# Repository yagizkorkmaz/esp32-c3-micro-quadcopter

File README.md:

# ESP32-C3 Micro Quadcopter

A brushed-motor micro quadcopter built around a custom flight-controller PCB: ESP32-C3 SuperMini, MPU-6050 IMU, a buck-boost regulator that keeps the MCU alive when the battery sags, and four low-side MOSFET motor drivers.

**Status: in progress.** Rev A boards are fabricated. Next: assembly, bring-up and flight firmware.

*Rev A, as it came back from the fab.*

## Hardware overview

```
1S LiPo ──┬── TPS63001 buck-boost ── 3.3 V ──┬── ESP32-C3 SuperMini (flight control, planned ESP-NOW link)
          │                                  └── MPU-6050 IMU (I2C)
          ├── 47k / 47k divider ── ADC (battery voltage)
          └── motor + ──[8520 motor]── AO3400A ── GND      (x4, PWM from ESP32-C3)
```

| Item | Choice | Why |
|---|---|---|
| MCU | ESP32-C3 SuperMini module | Small, cheap, built-in radio for a planned ESP-NOW controller link |
| IMU | MPU-6050 (GY-521 module), I2C | 3-axis gyro + accelerometer for attitude estimation |
| Regulator | TI TPS63001 buck-boost, 1S LiPo → 3.3 V | Holds 3.3 V when motor current pulls the battery below 3.3 V, so the MCU does not brown out mid-flight |
| Inductor | 2.2 µH, Bourns SRN4018-2R2M | Value from the TPS63001 reference design |
| Motor drivers | 4× AO3400A N-MOSFET, low side | Logic-level gate, driven directly by ESP32-C3 PWM |
| Gate network | 100 Ω series + 10 kΩ pull-down per MOSFET | Limits gate current; keeps the motors off while the MCU boots |
| Flyback diodes | 4× SS34 Schottky | Clamp the motor's inductive kick when the MOSFET turns off |
| Battery sense | 47 kΩ / 47 kΩ divider + 100 nF | Halves the cell voltage into the ADC range |
| Bulk capacitor | 220 µF / 6.3 V low-ESR | Buffers motor current transients on the battery rail |
| Motors | 4× 8520 coreless brushed, 3.7 V | |
| Battery | 1S LiPo | |

The TPS63001 section follows the TI reference design: the fixed 3.3 V version with FB tied to VOUT, a 100 Ω / 100 nF filter on VINA, EN and PS/SYNC tied to VINA, 10 µF at the input and 2× 10 µF at the output.

### ESP32-C3 pin map

| GPIO | Function |
|---|---|
| GPIO3 | Motor 1 PWM (Q1 gate via R1) |
| GPIO4 | Motor 2 PWM (Q2 gate via R3) |
| GPIO6 | Motor 3 PWM (Q3 gate via R5) |
| GPIO7 | Motor 4 PWM (Q4 gate via R7) |
| GPIO5 | MPU-6050 SDA |
| GPIO10 | MPU-6050 SCL |
| GPIO0 | Battery voltage (ADC, 47k / 47k divider) |

The MPU-6050 AD0 pin is tied to GND, so the IMU sits at I2C address 0x68. Its INT pin is not connected.

## PCB

| Item | Value |
|---|---|
| Size | 53 × 84 mm |
| Layers | 2 |
| Thickness | 0.8 mm as ordered (the board file still lists 1.6 mm) |
| Placement | All 34 components on the top side; all routing on the top layer |
| Ground | Ground pour on the bottom layer; SMD ground pads tied to it with 16 vias |
| Tool | KiCad |

KiCad 10 schematic and board files are in `hardware/`.

## Rev A notes

Found during design review after the boards were ordered. Each item has a fix that does not need a new board.

1. **ESP32-C3 GND pin is not connected.** The schematic symbol numbers its power pins `-1`, `-2`, `-3`, while the footprint pads are named `5V`, `G`, `3.3`. The pad names did not match, so the `G` pad got no net.
   *Rev A fix:* bridge the `G` pad to the ground pour on the bottom side with solder, or run a short wire to GND.
   *Rev B:* match the symbol pin numbers to the footprint and run ERC before ordering.
2. **Motor power runs on 0.2 mm tracks.** Every track on the board is 0.2 mm, including the battery-to-motor path. That is fine for signals, but four 8520 motors draw several amps, and the tracks to the far motors are 75–95 mm long.
   *Rev A fix:* wire from the battery `+` pad to each motor `+` pad.
   *Rev B:* route with the track tool and net classes instead of graphic lines on copper, with at least 1.5–2 mm for the battery rail and 1 mm for the motor and drain tracks.
3. **Battery and motors on 2.54 mm headers.** Header pins are rated for a few amps; the motors together can pull 8–10 A at full throttle.
   *Rev A fix:* solder the battery and motor leads directly to the pads.
   *Rev B:* use a high-current battery connector (BT2.0 / XT30).

## Bring-up plan

1. Before power: check continuity from `G` to battery `−`, and check for no short between battery `+` and `−`.
2. First power from a current-limited supply (3.7 V, 0.5 A limit) instead of the battery.
3. Confirm 3.3 V on the ESP32-C3 `3.3` pin, then flash.
4. Read the MPU-6050 over I2C.
5. Spin each motor on its own, propellers off.
6. Flight firmware: attitude estimation from the MPU-6050 and a PID loop driving the four motors, with an ESP-NOW link to a controller.

## Repository layout

```
hardware/   KiCad 10 schematic (drone.kicad_sch) and PCB (drone.kicad_pcb)
docs/       photos
```

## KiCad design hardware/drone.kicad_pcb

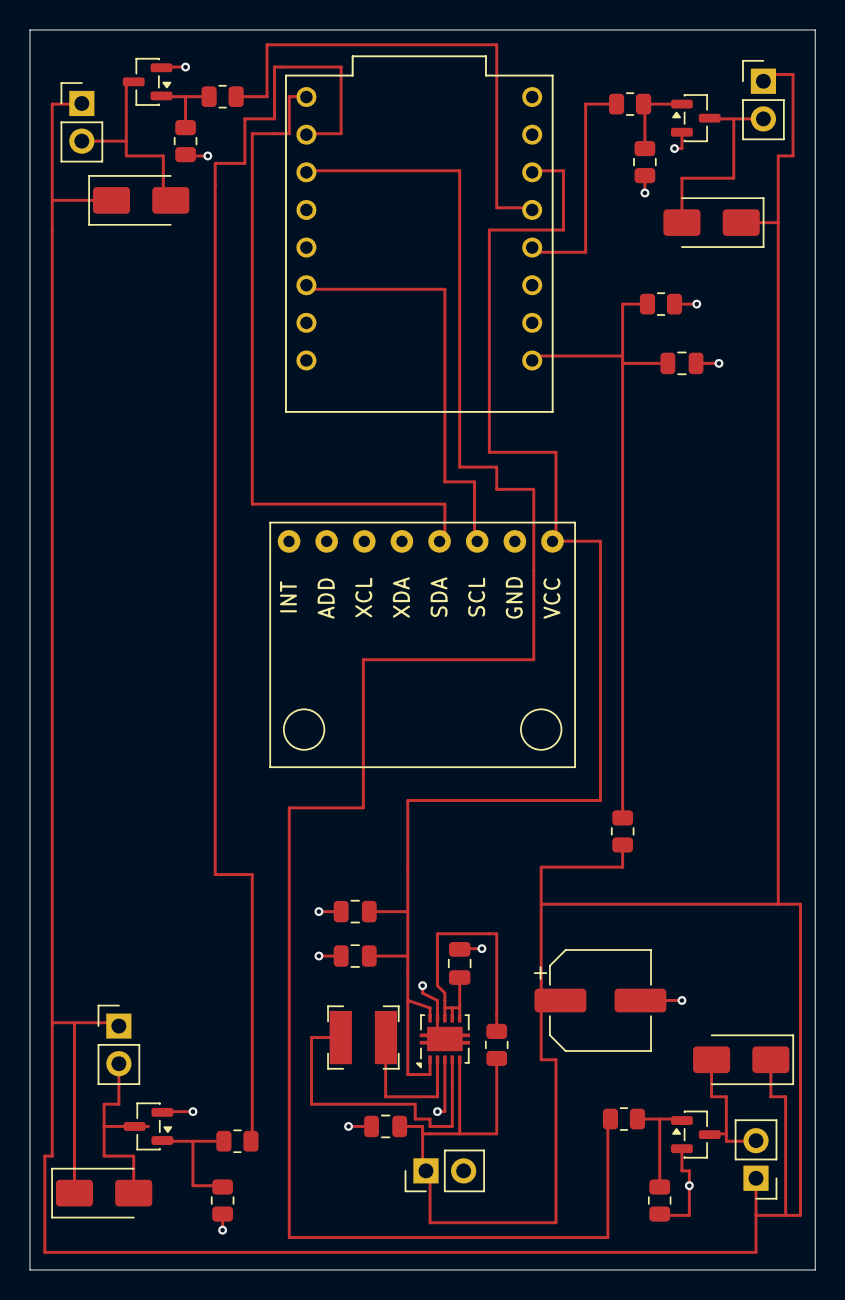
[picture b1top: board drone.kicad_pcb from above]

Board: 2 copper layers, 53.0 x 83.7 mm, 34 parts (0 on the bottom side), 21 nets, no tracks yet.

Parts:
C1, C2, C3: 10u; C_0805_2012Metric
C4, C6: 100n; C_0805_2012Metric
C5: 220u; CP_Elec_6.3x5.8
D1, D2, D3, D4: SS34; D_SMA
L1: 2.2u; L_Bourns-SRN4018
Q1, Q2, Q3, Q4: AO3400A; SOT-23
R1, R3, R5, R7, R9: 100; R_0805_2012Metric
R2, R4, R6, R8: 10k; R_0805_2012Metric
R10, R11: 47k; R_0805_2012Metric
U1: ESP32_C3_Super_Mini; MODULE_ESP32-C3_SUPERMINI_TH
U2: TPS63001; Texas_DRC0010J
U3: module_mpu6050
batarya1: Conn_01x02; PinHeader_1x02_P2.54mm_Vertical
motor1, motor2, motor3, motor4: Conn_01x02; PinHeader_1x02_P2.54mm_Vertical

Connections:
GND: C1.1, C2.2, C3.2, C4.1, C5.2, C6.2, Q1.2 (S), Q2.2 (S), Q3.2 (S), Q4.2 (S), R2.2, R4.2, R6.2, R8.2, R11.2, U2.3 (PGND), U2.9 (GND), U2.11 (PGND), U3.2 (GND), U3.7 (ADD), batarya1.2
unnamed: D1.2 (A), Q1.3 (D), motor1.2
unnamed: C1.2, C5.1, D1.1 (K), D2.1 (K), D3.1 (K), D4.1 (K), R9.1, R10.1, U2.5 (VIN), batarya1.1, motor1.1, motor2.1, motor3.1, motor4.1
unnamed: D2.2 (A), Q2.3 (D), motor2.2
unnamed: D3.2 (A), Q3.3 (D), motor3.2
unnamed: D4.2 (A), Q4.3 (D), motor4.2
unnamed: Q1.1 (G), R1.2, R2.1
unnamed: Q2.1 (G), R3.2, R4.1
unnamed: Q3.1 (G), R5.2, R6.1
unnamed: Q4.1 (G), R7.2, R8.1
unnamed: C2.1, C3.1, U1.3.3, U2.1 (VOUT), U2.10 (FB), U3.1 (VCC)
unnamed: C6.1, R10.2, R11.1, U1.0 (GPIO0)
unnamed: R1.1, U1.3 (GPIO3)
unnamed: R3.1, U1.4 (GPIO4)
unnamed: U1.5 (GPIO5), U3.4 (SDA)
unnamed: R5.1, U1.6 (GPIO6)
unnamed: R7.1, U1.7 (GPIO7)
unnamed: U1.10 (GPIO10), U3.3 (SCL)
unnamed: C4.2, R9.2, U2.6 (EN), U2.7 (PS/SYNC), U2.8 (VINA)
unnamed: L1.1, U2.4 (L1)
unnamed: L1.2, U2.2 (L2)
